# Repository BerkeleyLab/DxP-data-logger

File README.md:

# DxP Data Logger Hardware (LoRa + Distributed Sensor Probes Interface)

This repository only contains the hardware for the DxP (Distributed sensor Profiling) data logger (i.e., the “logger / base station” main board that connects to a DxP sensor probe via a connector.

The sensor probe / sensor-array board designs for DxP probes are released in a separate repository: **[DxP Sensor Probes](https://github.com/BerkeleyLab/DxP-sensor-probes)**.

The firmware for the nRF52832 is released in a separate repository: **[DxP Firmware](https://github.com/BerkeleyLab/DxP-firmware)**.

---

## Hardware overview
Designed for low-power, distributed environmental sensing deployments using the system concept from:
- *Wielandt et al., “TDD LoRa and Delta Encoding in Low-Power Networks of Environmental Sensor Arrays for Temperature and Deformation Monitoring”* (2023)

**Main logger board capabilities:**
- **LoRa modem:** RFM95W (single-channel LoRa)
- **Wireless SoC:** Nordic **nRF52832** (BLE capable)
- **Timekeeping:** **PCF2129AT** RTC
- **On-board storage:** **4 MB SPI flash** (data buffering)
- **Power:** designed for **2× AA** operation (1.8 V – 3.6 V range); includes **load switching** (e.g., TPS22919) to reduce sleep power
- **Sensor/probe interface:** **I2C** to connect to distributed sensor probes (supports long arrays through an address bit shift register on the sensor probe).
- **Micro SD card slot with load switch** for extra storage (e.g., large sensor datasets) and/or for base-station workflows to store data from multiple devices in the network.

---

## Repository contents

### KiCad design files (schematic / PCB)
- `loggerhw_v5.0.sch`
- `loggerhw_v5.0.kicad_pcb`
- `loggerhw_v5.0.kicad_pro`
- `loggerhw_v5.0.kicad_prl`
- `loggerhw_v5.0.pro`

### KiCad libraries
- `symbol/`
- `footprints/`
- `fp-lib-table`
- `fp-info-cache/`
- `sym-lib-table`
- `loggerhw_v5.0-cache.lib`

### Production / fabrication exports
- `fab/`

### Documentation
- `README.md`
- `LICENSE.md`
- `users.md`

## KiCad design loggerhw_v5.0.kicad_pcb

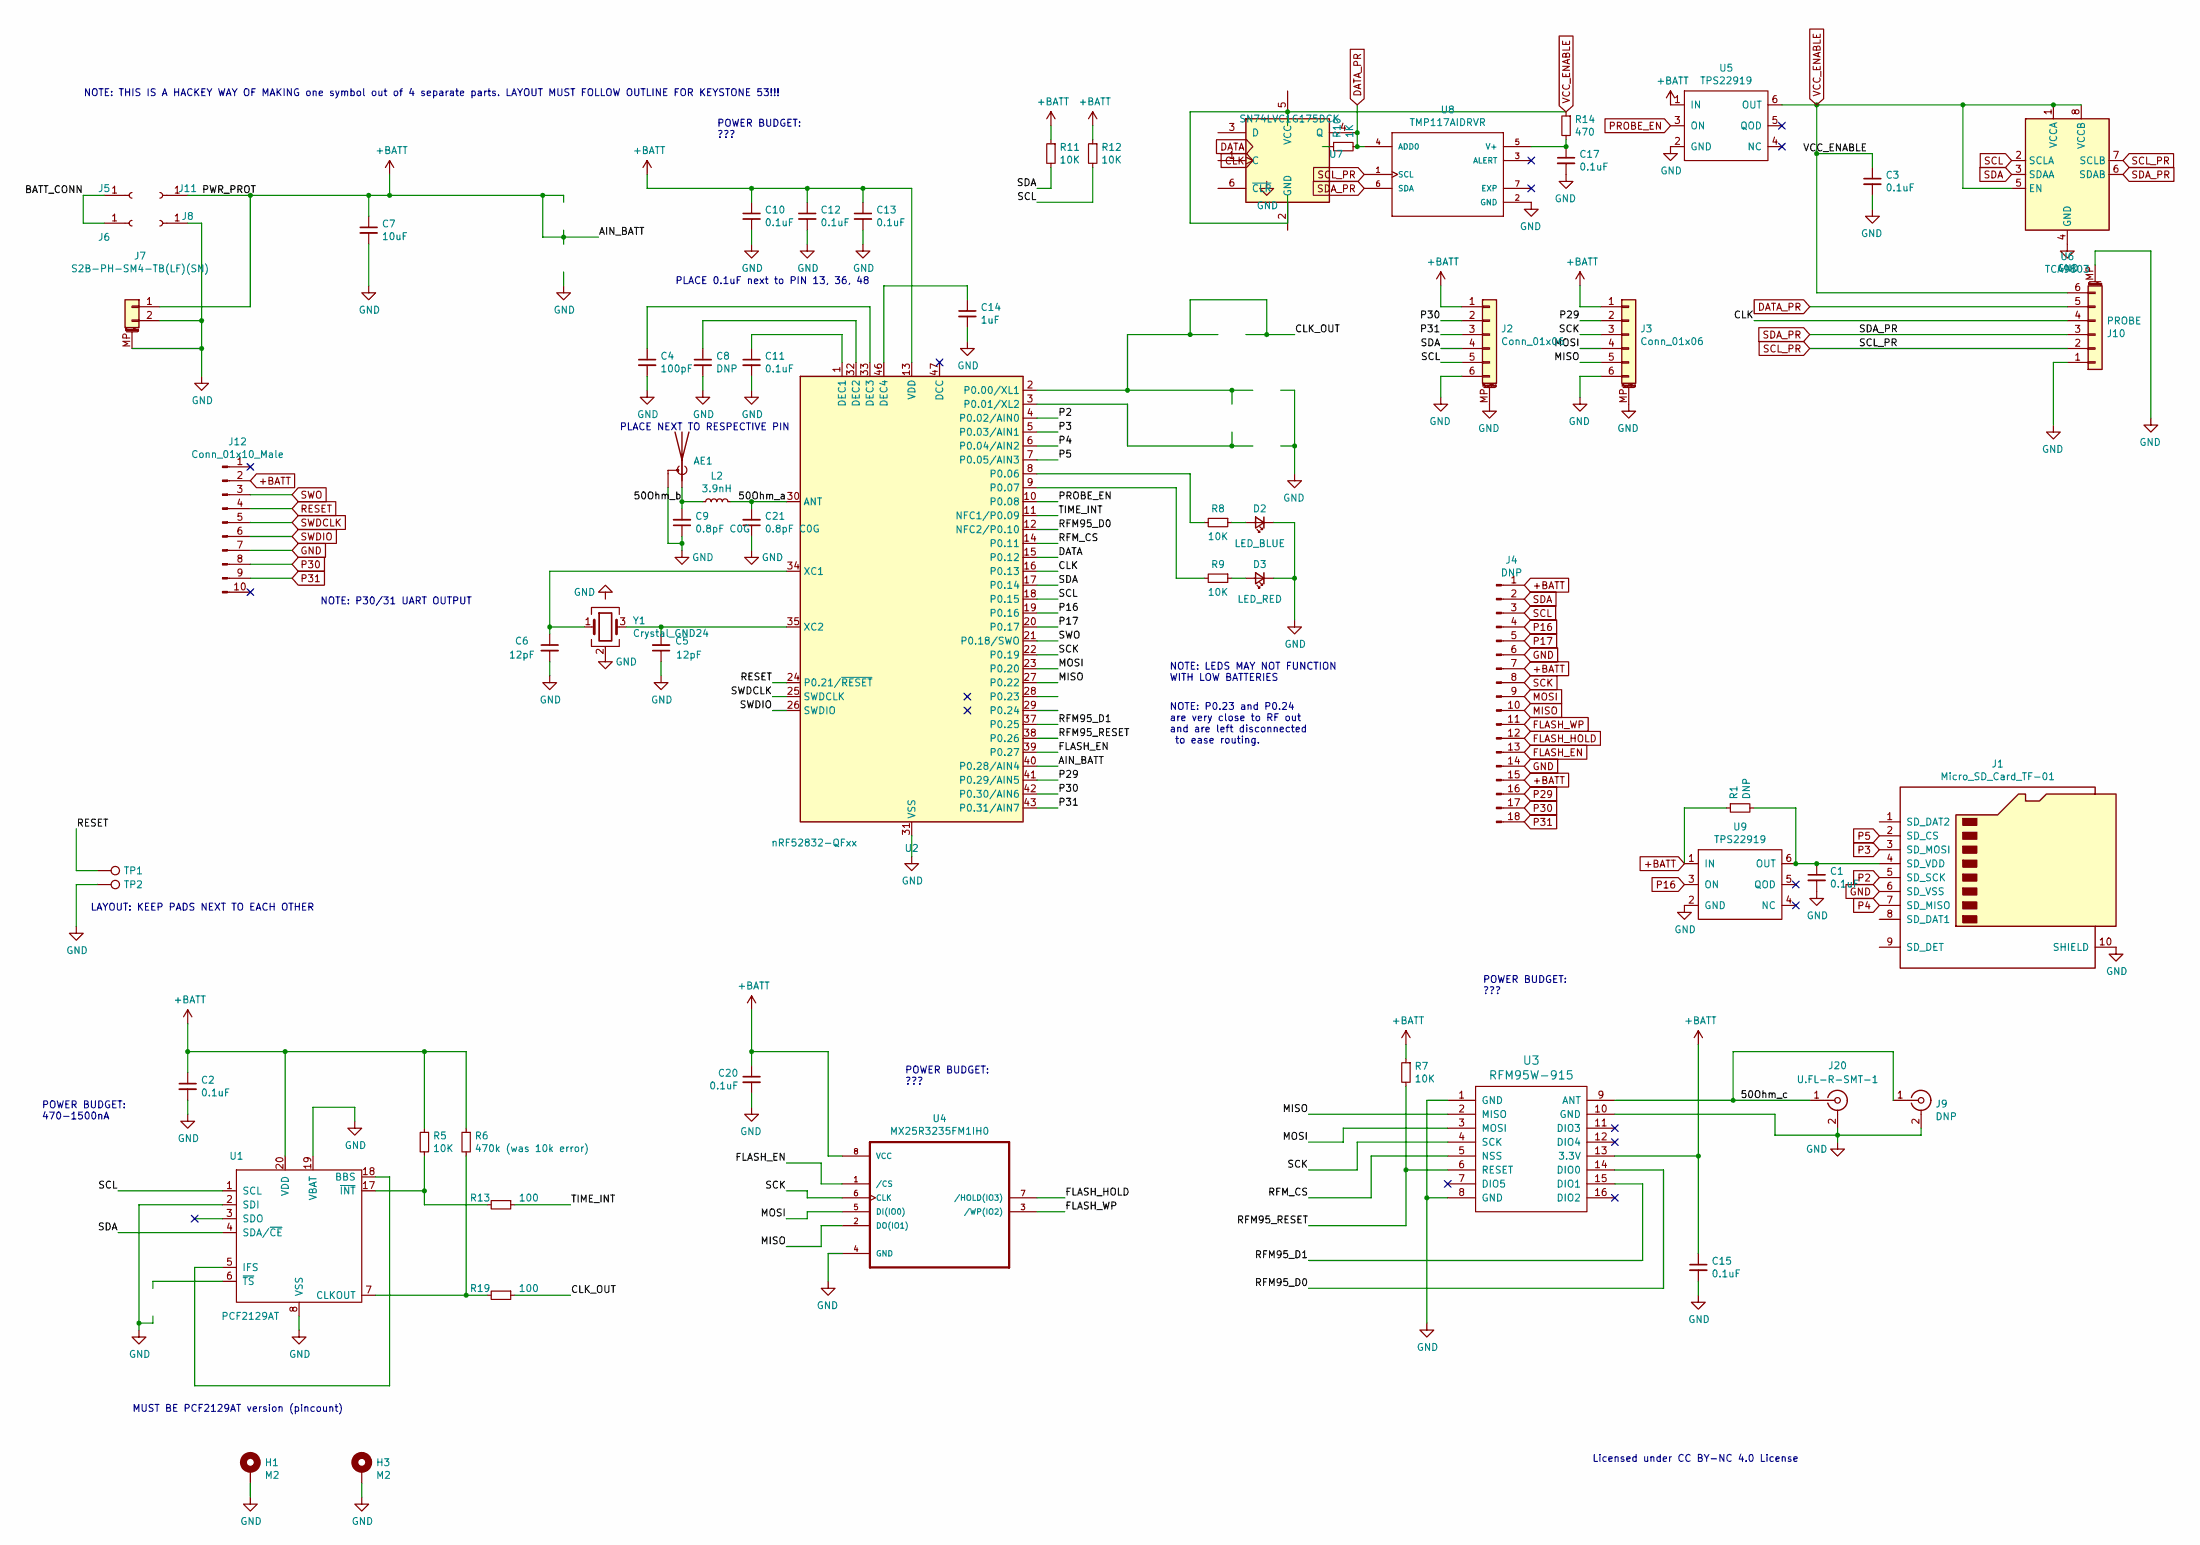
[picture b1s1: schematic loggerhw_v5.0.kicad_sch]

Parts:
AE1: Antenna_Shield; Texas_SWRA117D_2.4GHz_Right
C1, C2, C3, C10, C11, C12, C13, C15, C17, C20: 0.1uF; C_0402_1005Metric
C4: 100pF; C_0402_1005Metric
C5, C6: 12pF; C_0402_1005Metric
C7: 10uF; C_0603_1608Metric
C8: DNP; C_0402_1005Metric
C9, C21: 0.8pF C0G; C_0402_1005Metric
C14: 1uF; C_0402_1005Metric
D2: LED_BLUE; LED_0603_1608Metric
D3: LED_RED; LED_0603_1608Metric
H1, H3: M2; MountingHole_2.2mm_M2
J1: Micro_SD_Card_TF-01; TF-01A
J2, J3: Conn_01x06; JST_SH_BM06B-SRSS-TB_1x06-1MP_P1.00mm_Vertical
J4: DNP; PinHeader_1x18_P2.54mm_Vertical
J5, J6, J8, J11: Conn_01x01_Female; BK-53
J7: S2B-PH-SM4-TB(LF)(SN); JST_PH_B2B-PH-SM4-TB_1x02-1MP_P2.00mm_Vertical
J9: DNP; SMA_Samtec_SMA-J-P-X-ST-EM1_EdgeMount
J10: PROBE; JST_SH_SM06B-SRSS-TB_1x06-1MP_P1.00mm_Horizontal
J12: Conn_01x10_Male; 1x10pin ICSP 2.54mm
J20: U.FL-R-SMT-1; U.FL_Hirose_U.FL-R-SMT-1_Vertical
L2: 3.9nH; L_0402_1005Metric
R1: DNP; R_0402_1005Metric
R5, R7, R8, R9, R11, R12: 10K; R_0402_1005Metric
R6: 470k (was 10k error); R_0402_1005Metric
R10: 1K; R_0402_1005Metric
R13, R19: 100; R_0402_1005Metric
R14: 470; R_0402_1005Metric
TP1, TP2: TestPoint; TestPoint_Pad_D1.0mm
U1: PCF2129AT; SOIC-20W_7.5x12.8mm_P1.27mm
U2: nRF52832-QFxx; QFN-48-1EP_6x6mm_P0.4mm_EP4.66x4.66mm
U3: RFM95W-915; XCVR_RFM95W-915S2
U4: MX25R3235FM1IH0; SOIC-8_3.9x4.9mm_P1.27mm
U5, U9: TPS22919; Texas_R-PDSO-G6
U6: TCA9803; VSSOP-8_3.0x3.0mm_P0.65mm
U7: SN74LVC1G175DCK; Texas_R-PDSO-G6
U8: TMP117AIDRVR; WSON-6-1EP_2x2mm_P0.65mm_EP1x1.6mm
Y1: Crystal_GND24; Crystal_SMD_2016-4Pin_2.0x1.6mm

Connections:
+BATT: C2.1, C7.1, C10.1, C12.1, C13.1, C15.1, C20.1, J2.1, J3.1, J4.1, J4.7, J4.15, J7.1, J11.1, J12.2, R1.1, R5.1, R6.1, R7.1, R11.1, R12.1, U1.20 (VDD), U2.13 (VDD), U2.36 (VDD), U2.40 (P0.28/AIN4), U2.48 (VDD), U3.13 (3.3V), U4.8 (VCC), U5.1 (IN), U9.1 (IN)
/50Ohm_a: C21.2, L2.2, U2.30 (ANT)
/50Ohm_b: AE1.1 (A), C9.2, L2.1
/50Ohm_c: J9.1 (In), J20.1 (In), U3.9 (ANT)
/BATT_CONN: J5.1, J6.1
/CLK_OUT: R19.1, U2.2 (P0.00/XL1)
/RFM95_D0: U2.12 (NFC2/P0.10), U3.14 (DIO0)
/RFM95_D1: U2.37 (P0.25), U3.15 (DIO1)
/RFM95_RESET: R7.2, U2.38 (P0.26), U3.6 (RESET)
/RFM_CS: U2.14 (P0.11), U3.5 (NSS)
/TIME_INT: R13.1, U2.11 (NFC1/P0.09)
CLK: J10.4, U2.16 (P0.13), U7.1 (C)
DATA: U2.15 (P0.12), U7.3 (D)
FLASH_EN: J4.13, U2.39 (P0.27), U4.1 (/CS)
FLASH_HOLD: J4.12, U4.7 (/HOLD(IO3))
FLASH_WP: J4.11, U4.3 (/WP(IO2))
GND: AE1.2 (Shield), C1.2, C2.2, C3.2, C4.2, C5.1, C6.2, C7.2, C8.2, C9.1, C10.2, C11.2, C12.2, C13.2, C14.2, C15.2, C17.2, C20.2, C21.1, D2.1 (K), D3.1 (K), H1.1, H3.1, J1.6 (SD_VSS), J1.10 (SHIELD), J2.6, J2.MP (MountPin), J3.6, J3.MP (MountPin), J4.6, J4.14, J7.2, J7.MP (MountPin), J8.1, J9.2 (Ext), J10.1, J10.MP (MountPin), J12.7, J20.2 (Ext), TP2.1, U1.2 (SDI), U1.8 (VSS), U1.19 (VBAT), U2.31 (VSS), U2.45 (VSS), U2.49 (VSS), U3.1 (GND), U3.8 (GND), U3.10 (GND), U4.4 (GND), U5.2 (GND), U6.4 (GND), U7.2 (GND), U8.2 (GND), U9.2 (GND), Y1.2 (G), Y1.4 (G)
MISO: J3.5, J4.10, U2.27 (P0.22), U3.2 (MISO), U4.2 (DO(IO1))
MOSI: J3.4, J4.9, U2.23 (P0.20), U3.3 (MOSI), U4.5 (DI(IO0))
unnamed: C1.1, J1.4 (SD_VDD), R1.2, U9.6 (OUT)
unnamed: C4.1, U2.33 (DEC3)
unnamed: C5.2, U2.35 (XC2), Y1.3
unnamed: C6.1, U2.34 (XC1), Y1.1
unnamed: C8.1, U2.32 (DEC2)
unnamed: C11.1, U2.1 (DEC1)
unnamed: C14.1, U2.46 (DEC4)
unnamed: C17.1, R14.2, U8.5 (V+)
unnamed: D2.2 (A), R8.1
unnamed: D3.2 (A), R9.1
unnamed: R8.2, U2.8 (P0.06)
unnamed: R9.2, U2.9 (P0.07)
unnamed: R5.2, R13.2, U1.17 (~INT)
unnamed: R6.2, R19.2, U1.7 (CLKOUT)
unnamed: U1.5 (IFS), U1.18 (BBS)
P2: J1.5 (SD_SCK), U2.4 (P0.02/AIN0)
P3: J1.3 (SD_MOSI), U2.5 (P0.03/AIN1)
P4: J1.7 (SD_MISO), U2.6 (P0.04/AIN2)
P5: J1.2 (SD_CS), U2.7 (P0.05/AIN3)
P16: J4.4, U2.19 (P0.16), U9.3 (ON)
P17: J4.5, U2.20 (P0.17)
P29: J3.2, J4.16, U2.41 (P0.29/AIN5)
P30: J2.2, J4.17, J12.8, U2.42 (P0.30/AIN6)
P31: J2.3, J4.18, J12.9, U2.43 (P0.31/AIN7)
PROBE_EN: U2.10 (P0.08), U5.3 (ON)
RESET: J12.4, TP1.1, U2.24 (P0.21/~RESET)
SCK: J3.3, J4.8, U2.22 (P0.19), U3.4 (SCK), U4.6 (CLK)
SCL: J2.5, J4.3, R12.2, U1.1 (SCL), U2.18 (P0.15), U6.2 (SCLA)
SCL_PR: J10.2, U6.7 (SCLB), U8.1 (SCL)
SDA: J2.4, J4.2, R11.2, U1.4 (SDA/~CE), U2.17 (P0.14), U6.3 (SDAA)
SDA_PR: J10.3, U6.6 (SDAB), U8.6 (SDA)
SWDCLK: J12.5, U2.25 (SWDCLK)
SWDIO: J12.6, U2.26 (SWDIO)
SWO: J12.3, U2.21 (P0.18/SWO)
VCC_ENABLE: C3.1, J10.6, R14.1, U5.6 (OUT), U6.1 (VCCA), U6.5 (EN), U6.8 (VCCB), U7.5 (VCC), U7.6 (~CLR)

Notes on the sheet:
NOTE: THIS IS A HACKEY WAY OF MAKING one symbol out of 4 separate parts. LAYOUT MUST FOLLOW OUTLINE FOR KEYSTONE 53!!!
LAYOUT: KEEP PADS NEXT TO EACH OTHER
PLACE 0.1uF next to PIN 13, 36, 48
NOTE: P0.23 and P0.24 are very close to RF out and are left disconnected to ease routing.
NOTE: LEDS MAY NOT FUNCTION WITH LOW BATTERIES
Licensed under CC BY-NC 4.0 License
POWER BUDGET: 470-1500nA
POWER BUDGET: ???
MUST BE PCF2129AT version (pincount)
PLACE NEXT TO RESPECTIVE PIN
NOTE: P30/31 UART OUTPUT

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
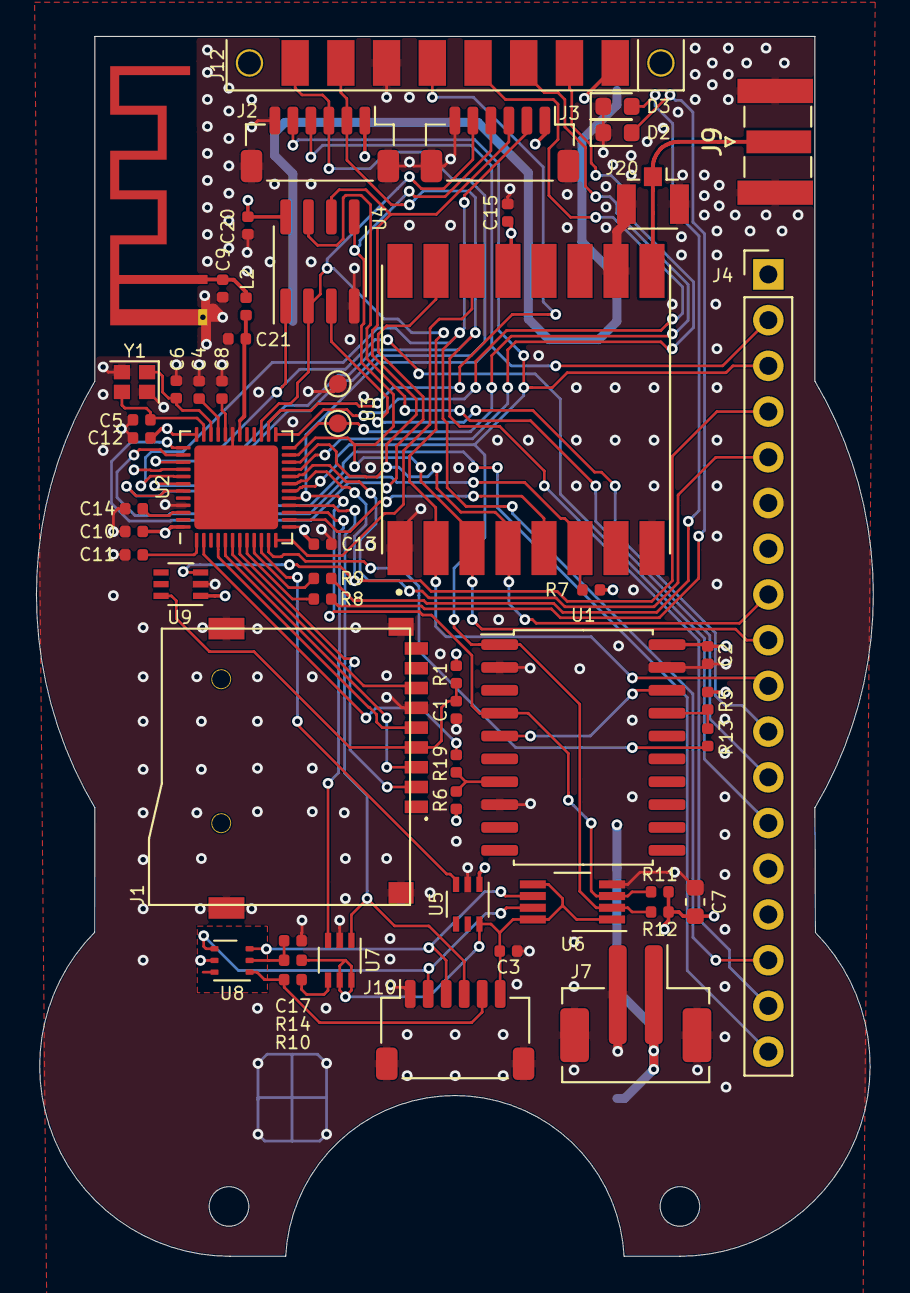
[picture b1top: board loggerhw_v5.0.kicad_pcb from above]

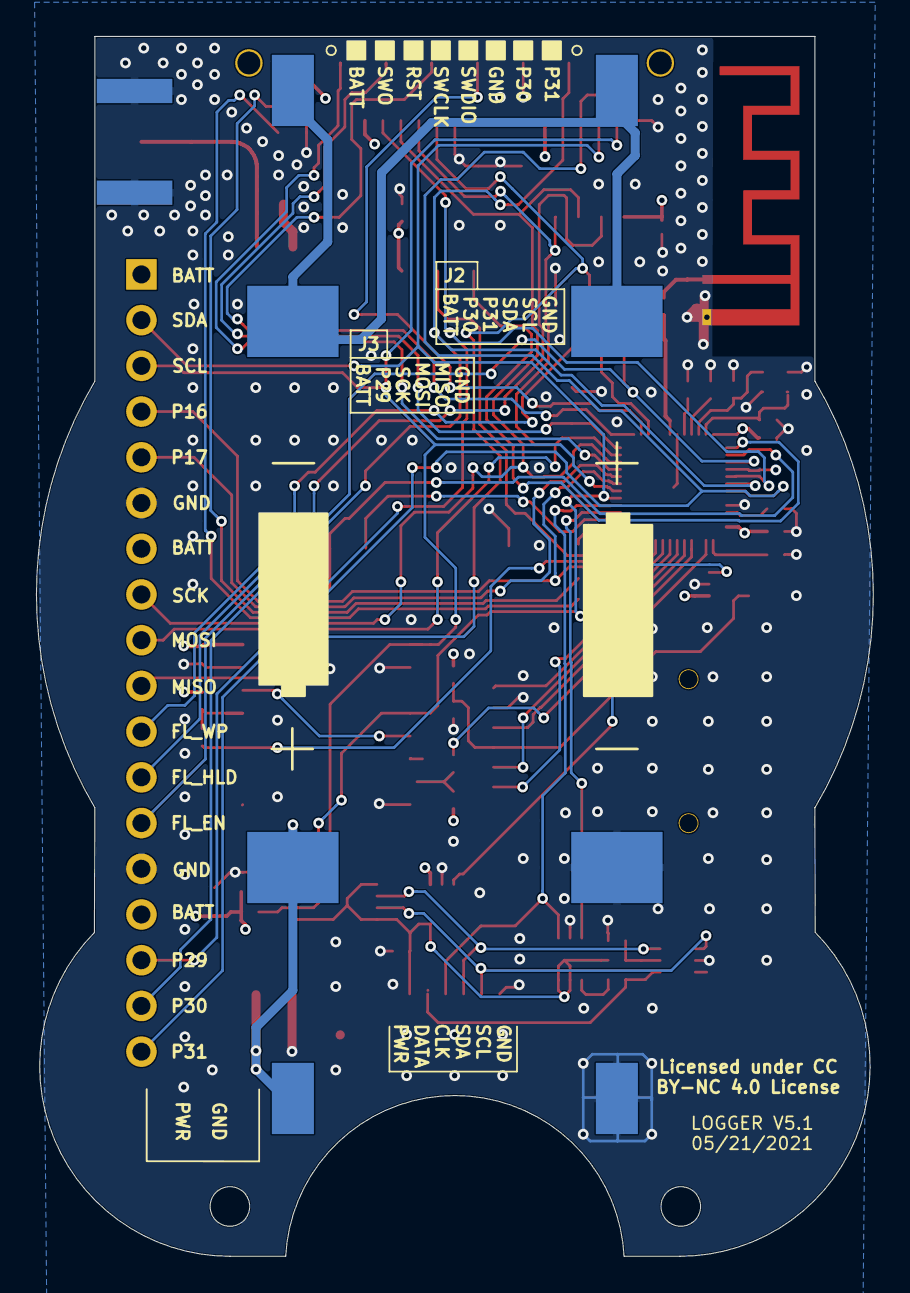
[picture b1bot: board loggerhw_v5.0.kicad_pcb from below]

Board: 4 copper layers, 46.5 x 67.8 mm, 61 parts (4 on the bottom side), 56 nets.

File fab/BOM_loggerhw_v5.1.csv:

"Id";"Designator";"Package";"Quantity";"Designation";"Supplier and ref";
1;"J1";"TF-01A";1;"Micro_SD_Card_TF-01";;;
2;"C1,C17,C3,C20,C15,C2,C11,C13,C12,C10";"C_0402_1005Metric";10;"0.1uF";;;
3;"J11,J8,J6,J5";"BK-53";4;"Conn_01x01_Female";;;
4;"U9,U5";"Texas_R-PDSO-G6";2;"TPS22919";;;
5;"Y1";"Crystal_SMD_2016-4Pin_2.0x1.6mm";1;"Crystal_GND24";;;
6;"U3";"XCVR_RFM95W-915S2";1;"RFM95W-915";;;
7;"U8";"WSON-6-1EP_2x2mm_P0.65mm_EP1x1.6mm";1;"TMP117AIDRVR";;;
8;"R12,R9,R11,R8,R7,R5";"R_0402_1005Metric";6;"10K";;;
9;"U7";"Texas_R-PDSO-G6";1;"SN74LVC1G175DCK";;;
10;"R14";"R_0402_1005Metric";1;"470";;;
11;"R10";"R_0402_1005Metric";1;"1K";;;
12;"U6";"VSSOP-8_3.0x3.0mm_P0.65mm";1;"TCA9803";;;
13;"J7";"JST_PH_B2B-PH-SM4-TB_1x02-1MP_P2.00mm_Vertical";1;"S2B-PH-SM4-TB(LF)(SN)";;;
14;"J12";"1x10pin ICSP 2.54mm";1;"Conn_01x10_Male";;;
15;"D2";"LED_0603_1608Metric";1;"LED_BLUE";;;
16;"U1";"SOIC-20W_7.5x12.8mm_P1.27mm";1;"PCF2129AT";;;
17;"J10";"JST_SH_SM06B-SRSS-TB_1x06-1MP_P1.00mm_Horizontal";1;"PROBE";;;
18;"R19,R13";"R_0402_1005Metric";2;"100";;;
19;"R6";"R_0402_1005Metric";1;"470k";;;
20;"J3,J2";"JST_SH_BM06B-SRSS-TB_1x06-1MP_P1.00mm_Vertical";2;"Conn_01x06";;;
21;"D3";"LED_0603_1608Metric";1;"LED_RED";;;
22;"C7";"C_0603_1608Metric";1;"10uF";;;
23;"U2";"QFN-48-1EP_6x6mm_P0.4mm_EP4.66x4.66mm";1;"nRF52832-QFxx";;;
24;"J20";"U.FL_Hirose_U.FL-R-SMT-1_Vertical";1;"U.FL-R-SMT-1";;;
25;"C21,C9";"C_0402_1005Metric";2;"0.8pF C0G";;;
26;"L2";"L_0402_1005Metric";1;"3.9nH";;;
27;"C14";"C_0402_1005Metric";1;"1uF";;;
28;"C6,C5";"C_0402_1005Metric";2;"12pF";;;
29;"C4";"C_0402_1005Metric";1;"100pF";;;
30;"U4";"SOIC-8_3.9x4.9mm_P1.27mm";1;"MX25R3235FM1IH0";;;

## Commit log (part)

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2026-06-13 Initial push of the DxP v4.2 KiCad project, license, README.md, users.md, libraries, and fabrication files
2026-06-13 Stop tracking .history/
2026-06-13 Separate copyright/license from README.md into a separate LICENSE.md file
2026-06-14 Version 5.0 added LoRa base station provisions: SD card slot with load switch, expansion header, SMA connector and general improvements
2026-06-15 Fix user table format in users.md
2026-06-17 silk screen tweak
